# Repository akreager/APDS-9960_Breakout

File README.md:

APDS-9960_Breakout
==================
I am attempting to redesign the SparkFun APDS gesture sensor to better fit my needs.
I want to move the sensor as close as possible to the edge of the board and add a voltage regulator and level shifting components to make the board 5V safe.

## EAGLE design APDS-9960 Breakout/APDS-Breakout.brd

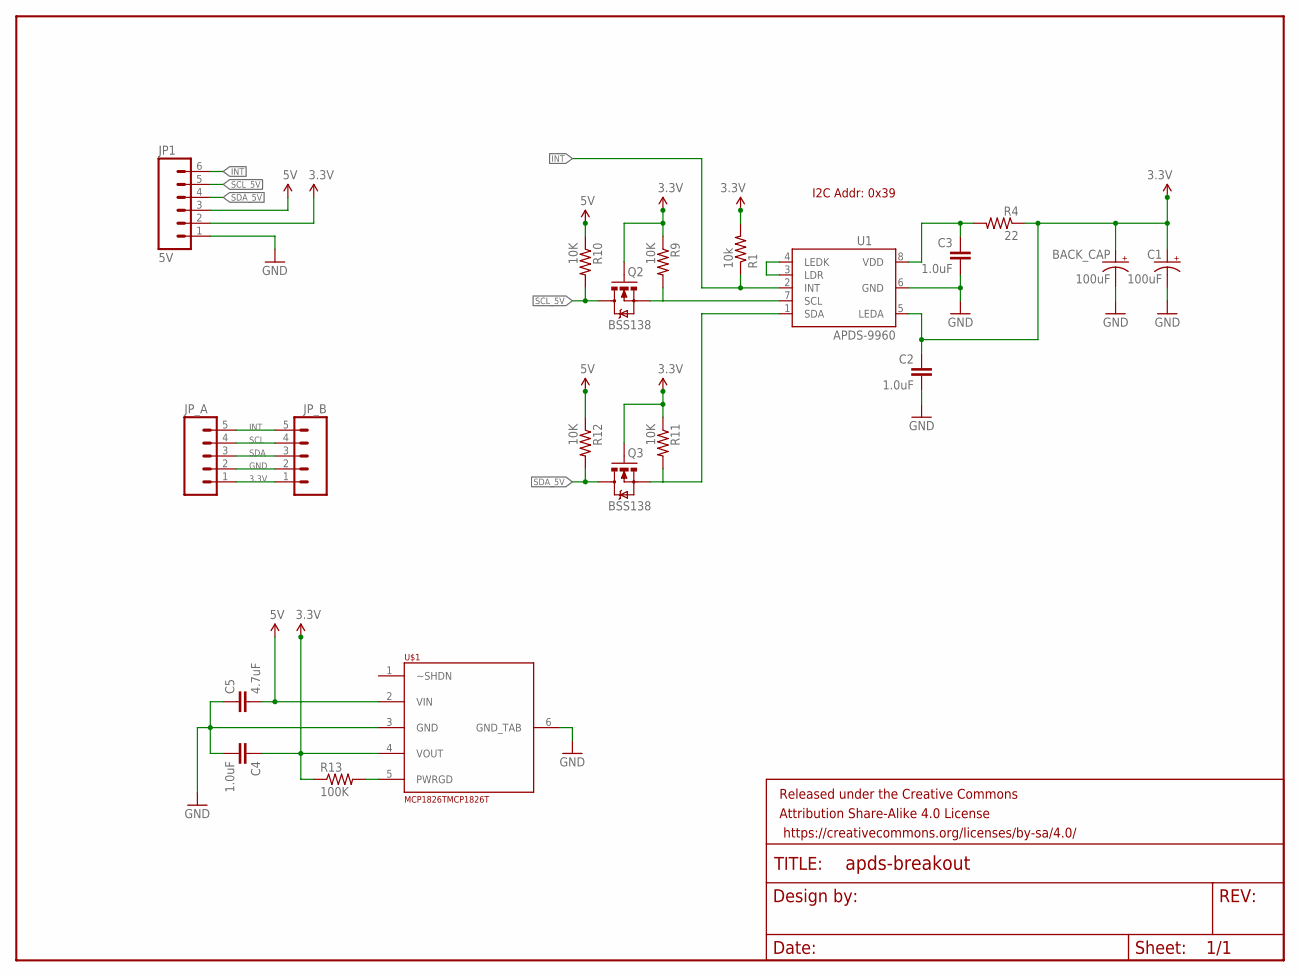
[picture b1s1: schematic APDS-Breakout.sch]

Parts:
BACK_CAP: 100uF; EIA7343
C1: 100uF; EIA7343
C2, C3, C4: 1.0uF; 0603-CAP
C5: 4.7uF; 0603-CAP
FRAME1: FRAME-LETTER; CREATIVE_COMMONS
JP1: 5V; 1X06_NO_SILK
JP_A: M05PTH; 1X05
JP_B: M05PTH; 1X05
Q2, Q3: BSS138; SOT23-3
R1: 10k; 0603-RES
R4: 22; 0603-RES
R9, R10, R11, R12: 10K; 0603-RES
R13: 100K; 0603-RES
U1: APDS-9960
U$1: MCP1826TMCP1826T; SOP-223-5

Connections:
3.3V: BACK_CAP.A (+), C1.A (+), C2.1, C4.1, JP1.2, JP_A.1, JP_B.1, Q2.1 (G), Q3.1 (G), R1.2, R4.1, R9.1, R11.1, R13.1, U1.5 (LEDA), U$1.4 (VOUT)
5V: C5.2, JP1.3, R10.1, R12.1, U$1.2 (VIN)
GND: BACK_CAP.C (-), C1.C (-), C2.2, C3.2, C4.2, C5.1, JP1.1, JP_A.2, JP_B.2, U1.6 (GND), U$1.3 (GND), U$1.6 (GND_TAB)
INT: JP1.6, JP_A.5, JP_B.5, R1.1, U1.2 (INT)
unnamed: C3.1, R4.2, U1.8 (VDD)
unnamed: U1.3 (LDR), U1.4 (LEDK)
unnamed: R13.2, U$1.5 (PWRGD)
SCL: JP_A.4, JP_B.4, Q2.2 (S), R9.2, U1.7 (SCL)
SCL_5V: JP1.5, Q2.3 (D), R10.2
SDA: JP_A.3, JP_B.3, Q3.2 (S), R11.2, U1.1 (SDA)
SDA_5V: JP1.4, Q3.3 (D), R12.2

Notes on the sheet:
I2C Addr: 0x39

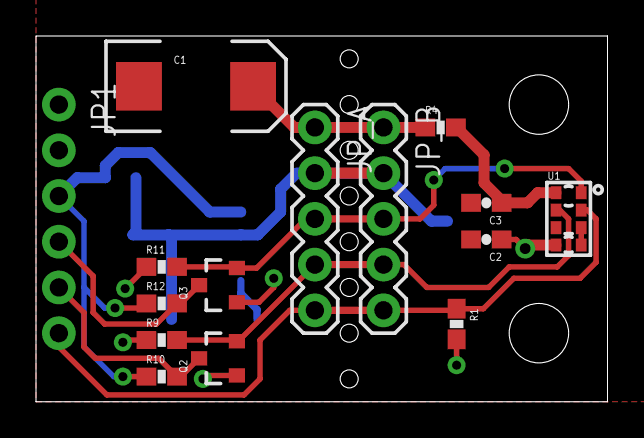
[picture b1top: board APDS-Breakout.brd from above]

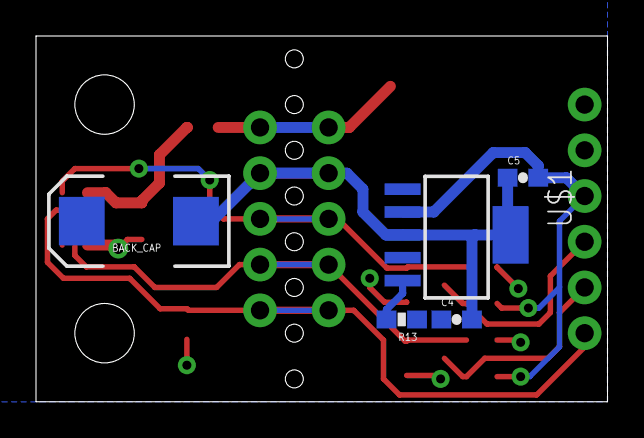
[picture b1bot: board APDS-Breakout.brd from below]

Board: 2 copper layers, 31.8 x 20.3 mm, 23 parts (5 on the bottom side), 11 nets.

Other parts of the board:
U$2, U$3: STAND-OFF

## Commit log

2014-12-01 :space_invader: Added .gitattributes & .gitignore files
2014-12-06 initial upload
2014-12-14 Initial Design Complete
    Modifications to the SparkFun design (most significant to least):
    1) Rotate and relocate sensor as close as possible to edge of board.
    Reason: I want to be able to put this sensor board into an enclosure
    next to an LCD. The sensor needs to be as close to the LCD for both to
    fit in the window.
    2) Add location on back of board for large electrolytic capacitor.

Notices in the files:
parts and their libraries:
SparkFun-Capacitors: Licensing: Creative Commons ShareAlike 4.0 International - https://creativecommons.org/licenses/by-sa/4.0
SparkFun-Aesthetics: Released under the Creative Commons Attribution Share-Alike 4.0 License
SparkFun-Aesthetics: https://creativecommons.org/licenses/by-sa/4.0
